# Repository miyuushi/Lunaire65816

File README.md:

# Lunaire65816

My 16-bit retro computer I designed from scratch. It's centered around a 65816 CPU and uses classic components with FPGA-based glue logic, hardware FM sound, and modern display output.

## Features

- 65816 16-bit CPU
- Custom PCB design
- FPGA for glue logic and video generation
- YM3812 FM synthesis sound chip
- Dual VIA chips for I/O
- SNES controller headers
- PS/2 keyboard interface
- VGA output

## Architecture Overview

- CPU: WDC 65816
- Sound: YM3812 (OPL2)
- I/O: Two VIA chips
- Video: VGA generated using FPGA logic
- Input:
  - SNES controller ports
  - PS/2 keyboard
- Address decoding: GAL
- Board: Custom PCB

## Memory Map

Address decoding is handled by a GAL chip.

### 6502 Emulation Mode

- 48K RAM
- 4K I/O
- 12K ROM

This mode is useful for compatibility and early bring-up.

### 65816 Native Mode

- 4MB RAM
- 4K I/O (expandable, may increase later)
- 12K ROM

Native mode enables the full 24-bit address space of the 65816.

## Audio

The system uses a YM3812 (OPL2) FM synthesis chip for hardware-generated sound.

## Input

- SNES controller headers for gamepad input
- PS/2 keyboard support

## Video (unimplemented)

VGA output is generated through FPGA logic. The goal is compatibility with modern monitors. 

## Screenshots

Hardware:

## Hardware Design Notes

- Custom PCB layout
- Discrete retro components
- FPGA used for glue logic and video
- GAL used for address decoding
- VIA chips provide timers and general-purpose I/O

## Status

Work in progress. Basic hardware is assembled and bring-up is ongoing.

## License

This project is licensed under the GNU Lesser General Public License v3.0 or later.

See the LICENSE file for details.

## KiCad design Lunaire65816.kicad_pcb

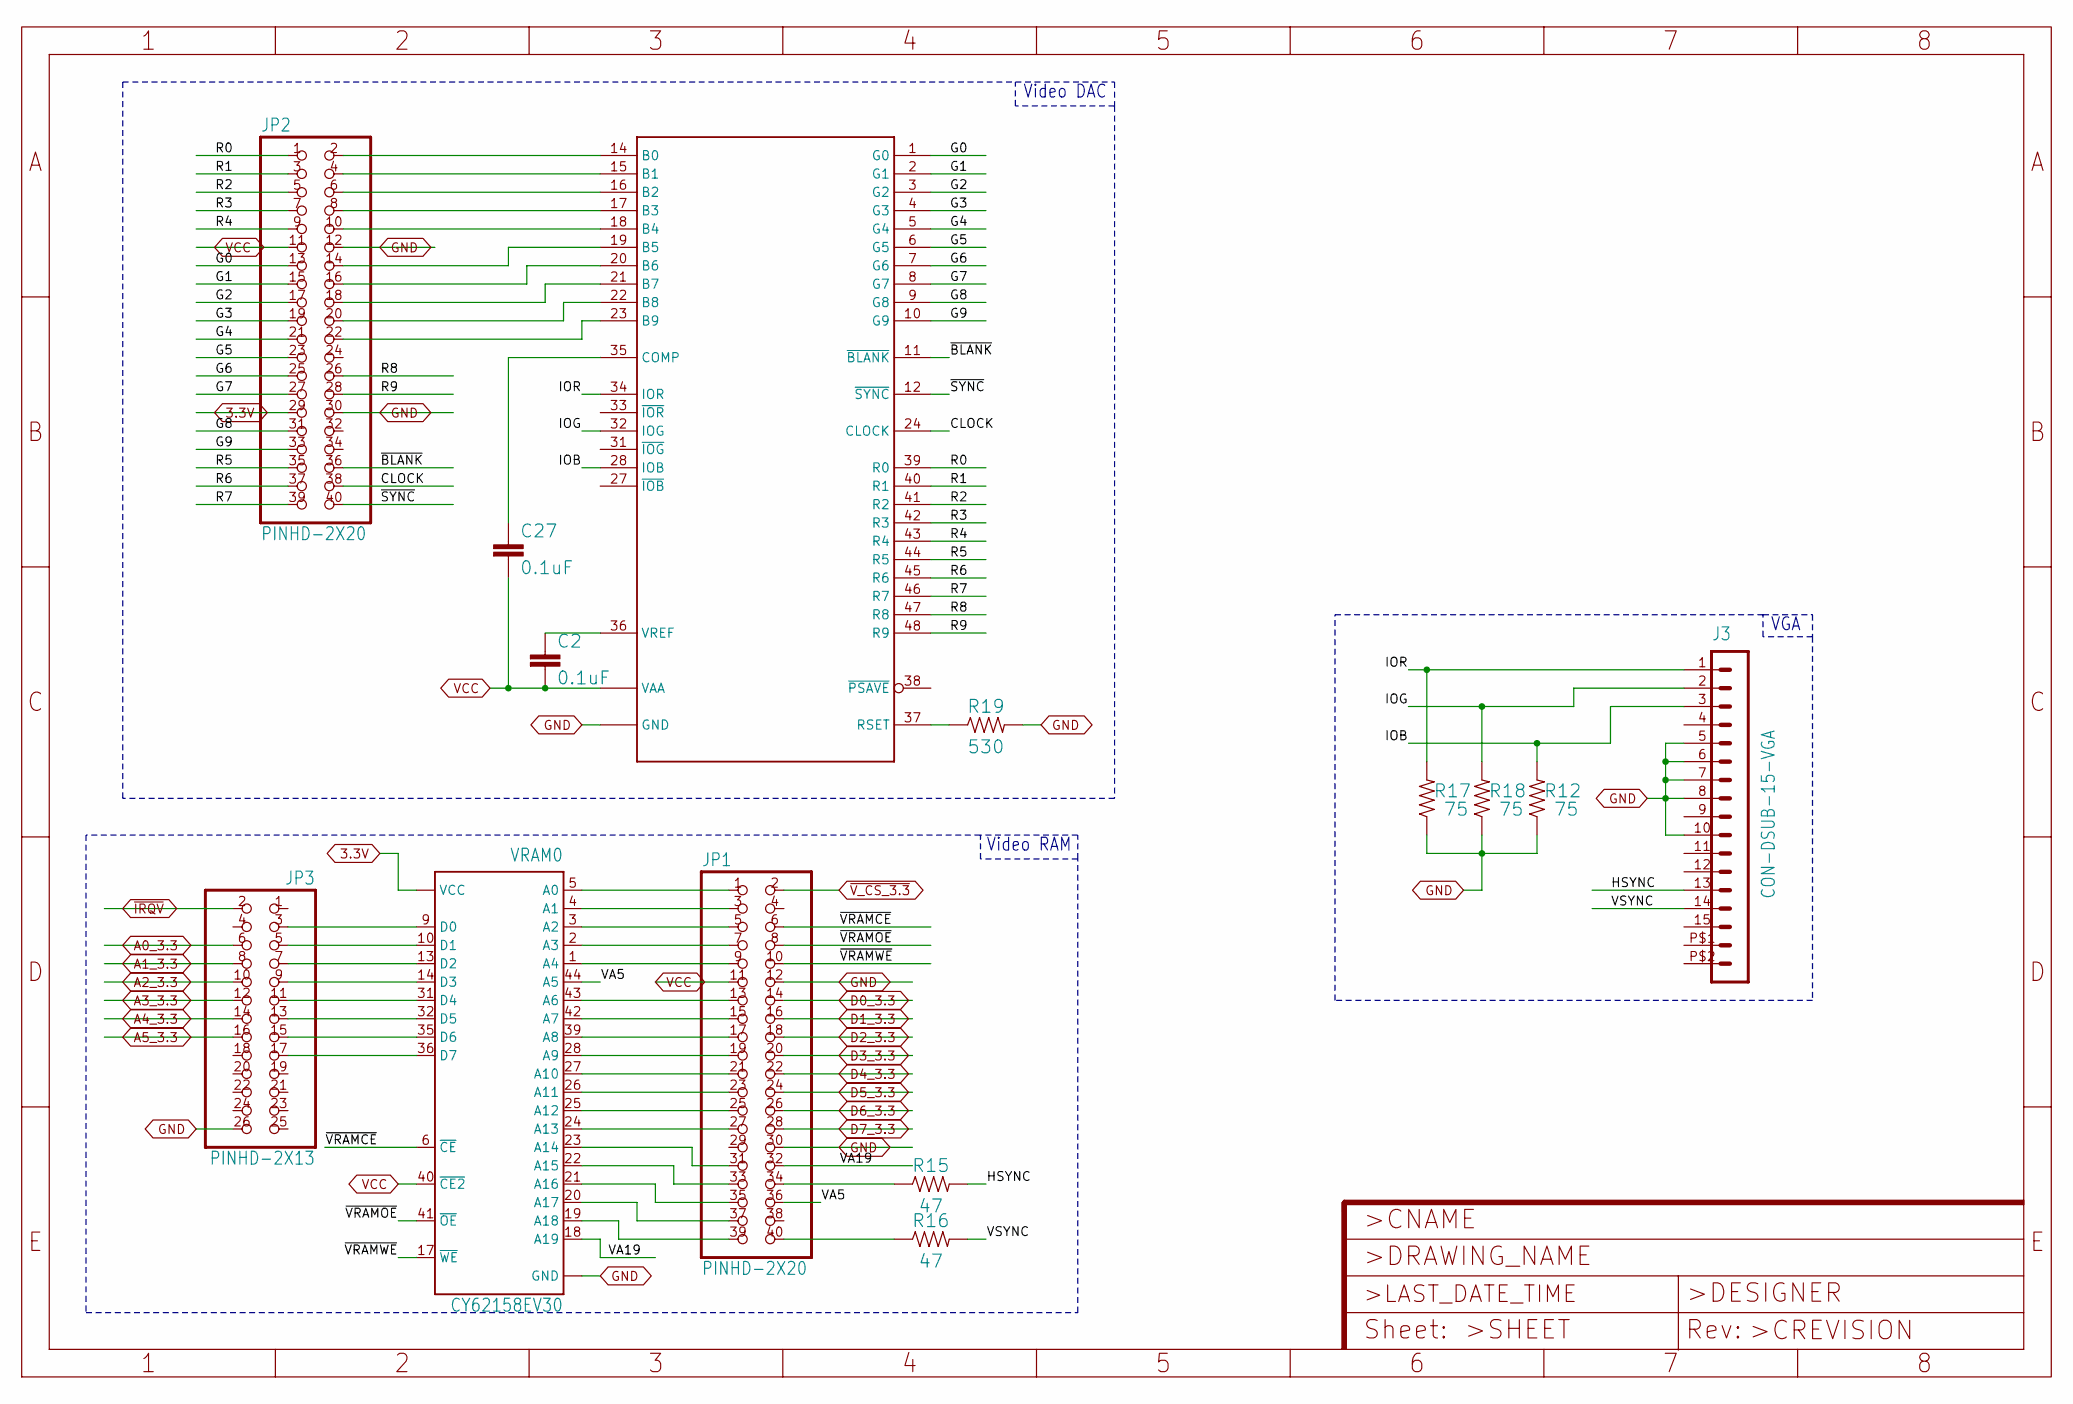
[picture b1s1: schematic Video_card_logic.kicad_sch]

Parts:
C2, C27: 0.1uF; 0603
IC2: ADV7123; LQFP48
J3: CON-DSUB-15-VGA; 181-015-212-171
JP1, JP2: PINHD-2X20; 2X20
JP3: PINHD-2X13; 2X13
R12, R17, R18: 75; 0603
R15, R16: 47; 0603
R19: 530; 0603
VRAM0: CY62158EV30; TSOP-II-44

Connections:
3.3V: JP2.29, VRAM0.11 (VCC), VRAM0.33 (VCC); also elsewhere on the board
A0_3.3: JP3.6; also elsewhere on the board
A1_3.3: JP3.8; also elsewhere on the board
A2_3.3: JP3.10; also elsewhere on the board
A3_3.3: JP3.12; also elsewhere on the board
A4_3.3: JP3.14; also elsewhere on the board
A5_3.3: JP3.16; also elsewhere on the board
CLOCK: IC2.24 (CLOCK), JP2.38
D0_3.3: JP1.14; also elsewhere on the board
D1_3.3: JP1.16; also elsewhere on the board
D2_3.3: JP1.18; also elsewhere on the board
D3_3.3: JP1.20; also elsewhere on the board
D4_3.3: JP1.22; also elsewhere on the board
D5_3.3: JP1.24; also elsewhere on the board
D6_3.3: JP1.26; also elsewhere on the board
D7_3.3: JP1.28; also elsewhere on the board
G0: IC2.1 (G0), JP2.13
G1: IC2.2 (G1), JP2.15
G2: IC2.3 (G2), JP2.17
G3: IC2.4 (G3), JP2.19
G4: IC2.5 (G4), JP2.21
G5: IC2.6 (G5), JP2.23
G6: IC2.7 (G6), JP2.25
G7: IC2.8 (G7), JP2.27
G8: IC2.9 (G8), JP2.31
G9: IC2.10 (G9), JP2.33
GND: IC2.25 (GND), IC2.26 (GND), J3.5, J3.6, J3.7, J3.8, J3.10, JP1.12, JP1.30, JP2.12, JP2.30, JP3.26, R12.1, R17.1, R18.1, R19.2, VRAM0.12 (GND), VRAM0.34 (GND); also elsewhere on the board
HSYNC: J3.13, R15.2
IOB: IC2.28 (IOB), J3.3, R12.2
IOG: IC2.32 (IOG), J3.2, R18.2
IOR: IC2.34 (IOR), J3.1, R17.2
unnamed: JP1.35, VRAM0.21 (A16)
unnamed: JP1.33, VRAM0.22 (A15)
unnamed: JP1.31, VRAM0.23 (A14)
unnamed: JP1.27, VRAM0.24 (A13)
unnamed: IC2.37 (RSET), R19.1
unnamed: C2.1, IC2.36 (VREF)
unnamed: JP1.37, VRAM0.20 (A17)
unnamed: IC2.14 (B0), JP2.2
unnamed: IC2.15 (B1), JP2.4
unnamed: IC2.16 (B2), JP2.6
unnamed: IC2.17 (B3), JP2.8
unnamed: IC2.18 (B4), JP2.10
unnamed: IC2.19 (B5), JP2.14
unnamed: IC2.20 (B6), JP2.16
unnamed: IC2.21 (B7), JP2.18
unnamed: IC2.22 (B8), JP2.20
unnamed: IC2.23 (B9), JP2.22
unnamed: C27.1, IC2.35 (COMP)
unnamed: JP1.40, R16.1
unnamed: JP1.34, R15.1
unnamed: JP1.25, VRAM0.25 (A12)
unnamed: JP1.23, VRAM0.26 (A11)
unnamed: JP1.21, VRAM0.27 (A10)
unnamed: JP1.19, VRAM0.28 (A9)
unnamed: JP1.17, VRAM0.39 (A8)
unnamed: JP1.15, VRAM0.42 (A7)
unnamed: JP1.13, VRAM0.43 (A6)
unnamed: JP1.9, VRAM0.1 (A4)
unnamed: JP1.7, VRAM0.2 (A3)
unnamed: JP1.5, VRAM0.3 (A2)
unnamed: JP3.17, VRAM0.36 (D7)
unnamed: JP3.15, VRAM0.35 (D6)
unnamed: JP3.13, VRAM0.32 (D5)
unnamed: JP3.11, VRAM0.31 (D4)
unnamed: JP3.9, VRAM0.14 (D3)
unnamed: JP3.7, VRAM0.13 (D2)
unnamed: JP3.5, VRAM0.10 (D1)
unnamed: JP3.3, VRAM0.9 (D0)
unnamed: JP1.39, VRAM0.19 (A18)
unnamed: JP1.3, VRAM0.4 (A1)
unnamed: JP1.1, VRAM0.5 (A0)
R0: IC2.39 (R0), JP2.1
R1: IC2.40 (R1), JP2.3
R2: IC2.41 (R2), JP2.5
R3: IC2.42 (R3), JP2.7
R4: IC2.43 (R4), JP2.9
R5: IC2.44 (R5), JP2.35
R6: IC2.45 (R6), JP2.37
R7: IC2.46 (R7), JP2.39
R8: IC2.47 (R8), JP2.26
R9: IC2.48 (R9), JP2.28
VA5: JP1.36, VRAM0.44 (A5)
VA19: JP1.32, VRAM0.18 (A19)
VCC: C2.2, C27.2, IC2.13 (VAA), IC2.29 (VAA), IC2.30 (VAA), JP1.11, JP2.11, VRAM0.40 (~CE2); also elsewhere on the board
VSYNC: J3.14, R16.2
~BLANK: IC2.11 (~BLANK), JP2.36
~IRQV: JP3.2; also elsewhere on the board
~SYNC: IC2.12 (~SYNC), JP2.40
~VRAMCE: JP1.6, VRAM0.6 (~CE)
~VRAMOE: JP1.8, VRAM0.41 (~OE)
~VRAMWE: JP1.10, VRAM0.17 (~WE)
~V_CS_3.3: JP1.2; also elsewhere on the board

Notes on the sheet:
VGA
Video DAC
Video RAM

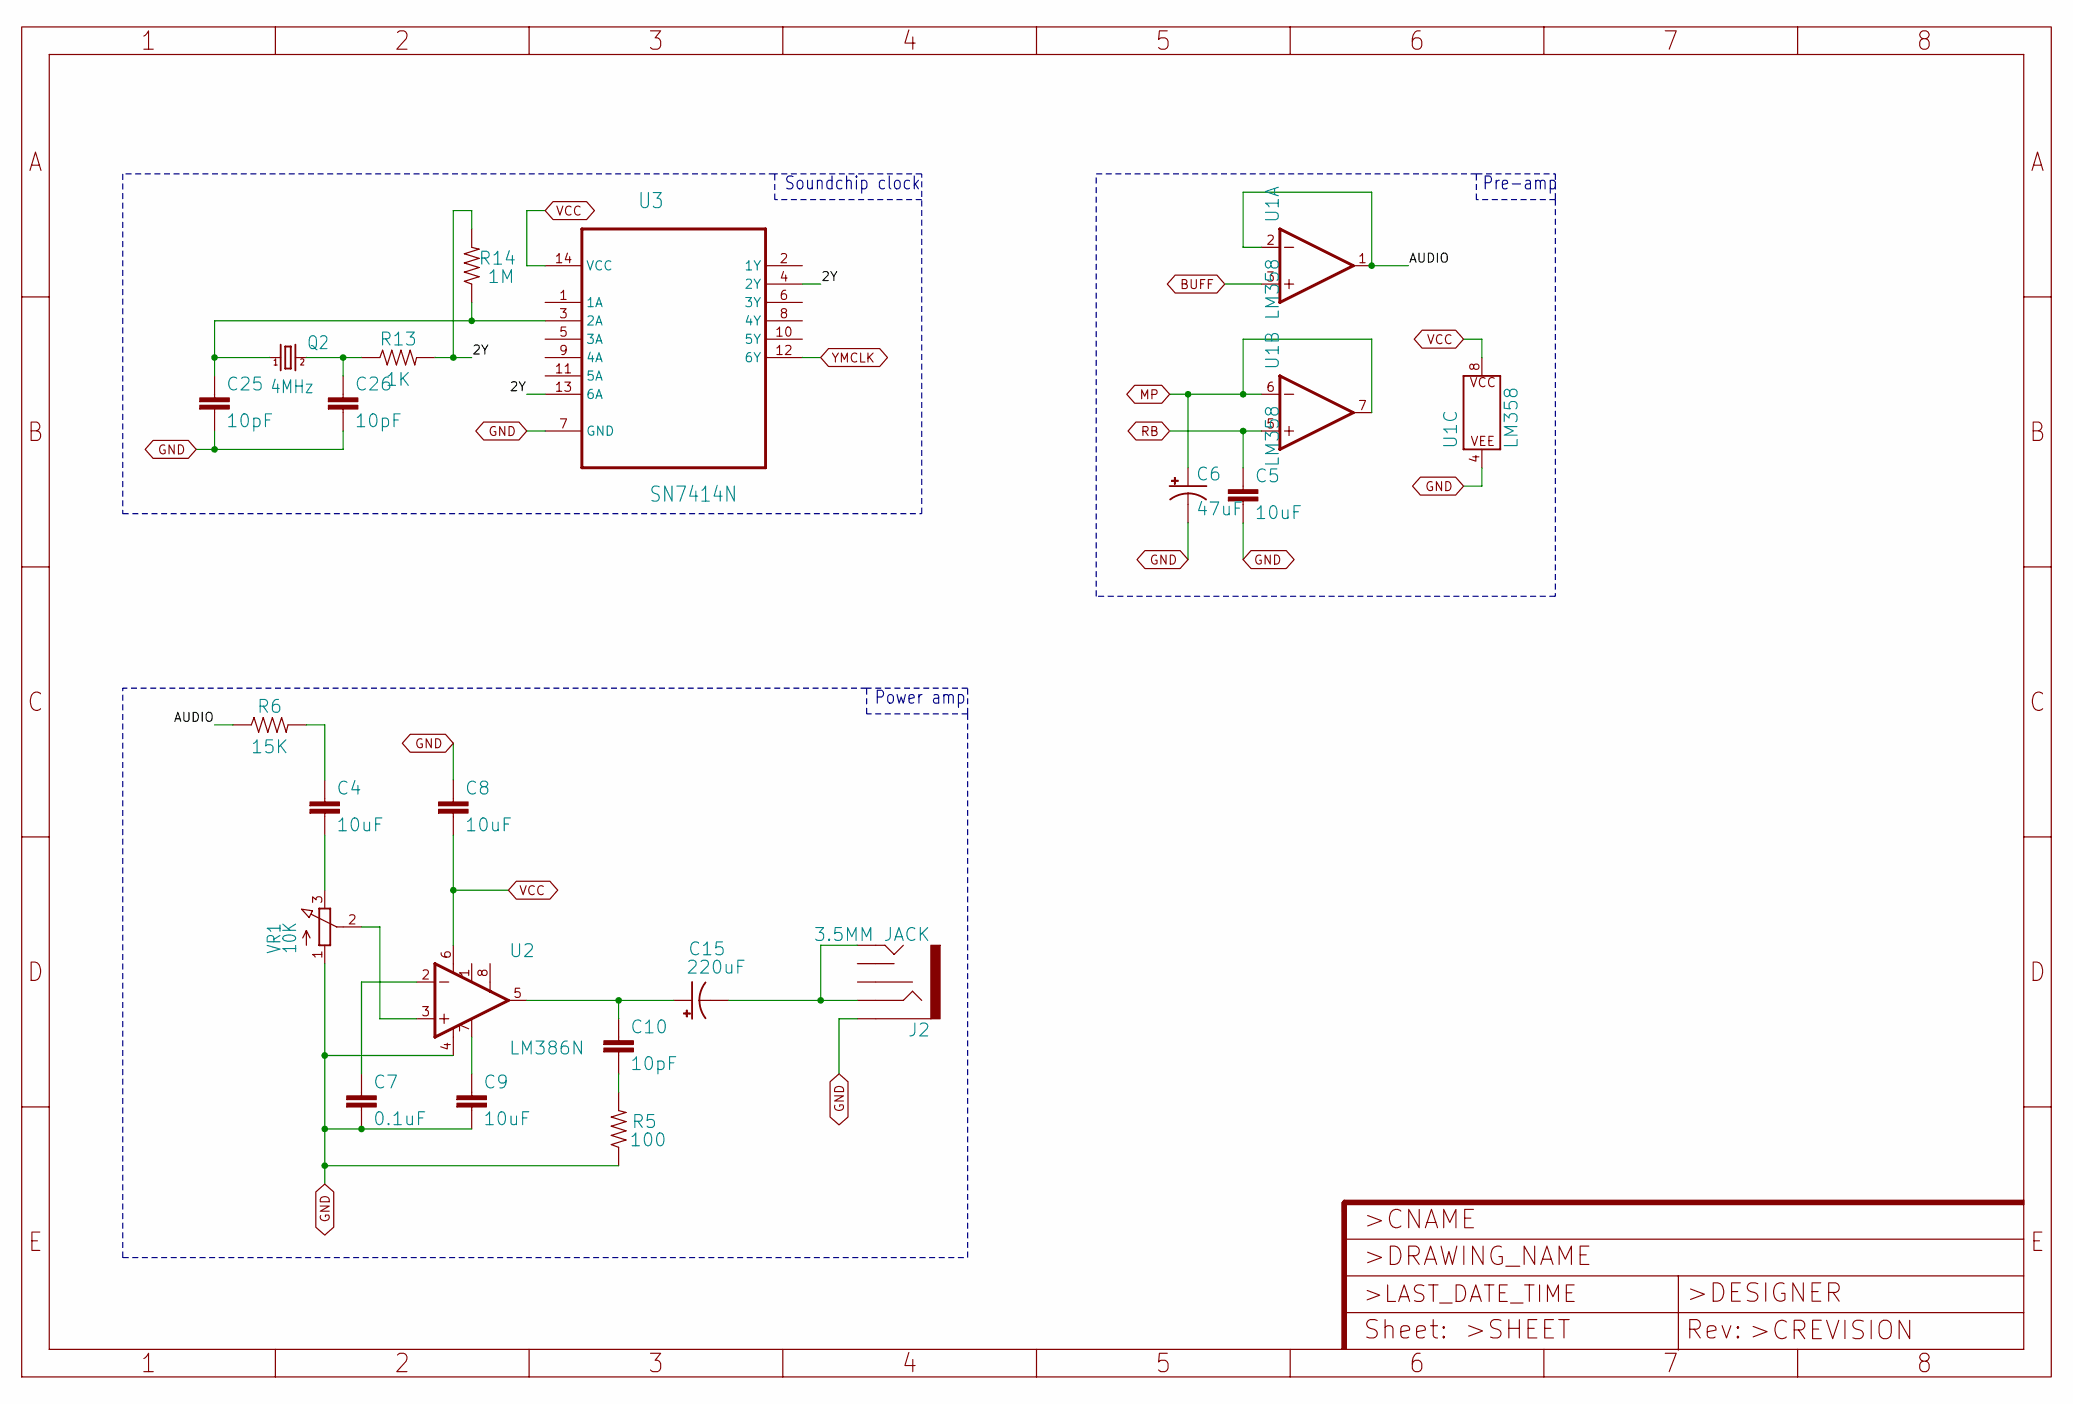
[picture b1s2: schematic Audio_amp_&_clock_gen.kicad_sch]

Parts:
C4, C5, C8, C9: 10uF; 0603
C6: 47uF; EIA3528
C7: 0.1uF; 0603
C10, C25, C26: 10pF; 0603
C15: 220uF; PANASONIC_D
J2: 3.5MM JACK; AUDIO-JACK
Q2: 4MHz; HC49_S
R5: 100; 0603
R6: 15K; 0603
R13: 1K; 0603
R14: 1M; 0603
U1: LM358; DIP08
U2: LM386N; DIP08
U3: SN7414N; DIP254P762X508-14
VR1: 10K; 3RP_1610N

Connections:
2Y: R13.2, R14.2, U3.4 (2Y), U3.13 (6A)
AUDIO: R6.1, U1.1 (OUT), U1.2 (-IN)
BUFF: U1.3 (+IN); also elsewhere on the board
GND: C5.2, C6.C (-), C7.2, C8.1, C9.2, C25.2, C26.2, J2.SLEEVE, R5.1, U1.4 (P$V-), U2.4 (V-), U3.7 (GND), VR1.1 (A); also elsewhere on the board
MP: C6.A (+), U1.6 (-IN), U1.7 (OUT); also elsewhere on the board
unnamed: C7.1, U2.2 (-IN)
unnamed: C4.1, R6.2
unnamed: C4.2, VR1.3 (E)
unnamed: U2.3 (+IN), VR1.2 (S)
unnamed: C9.1, U2.7 (BP)
unnamed: C10.1, C15.+, U2.5 (OUT)
unnamed: C10.2, R5.2
unnamed: C15.-, J2.RING, J2.TIP
unnamed: C25.1, Q2.1, R14.1, U3.3 (2A)
unnamed: C26.1, Q2.2, R13.1
RB: C5.1, U1.5 (+IN); also elsewhere on the board
VCC: C8.2, U1.8 (P$V+), U2.6 (V+), U3.14 (VCC); also elsewhere on the board
YMCLK: U3.12 (6Y); also elsewhere on the board

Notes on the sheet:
Power amp
Soundchip clock
Pre-amp

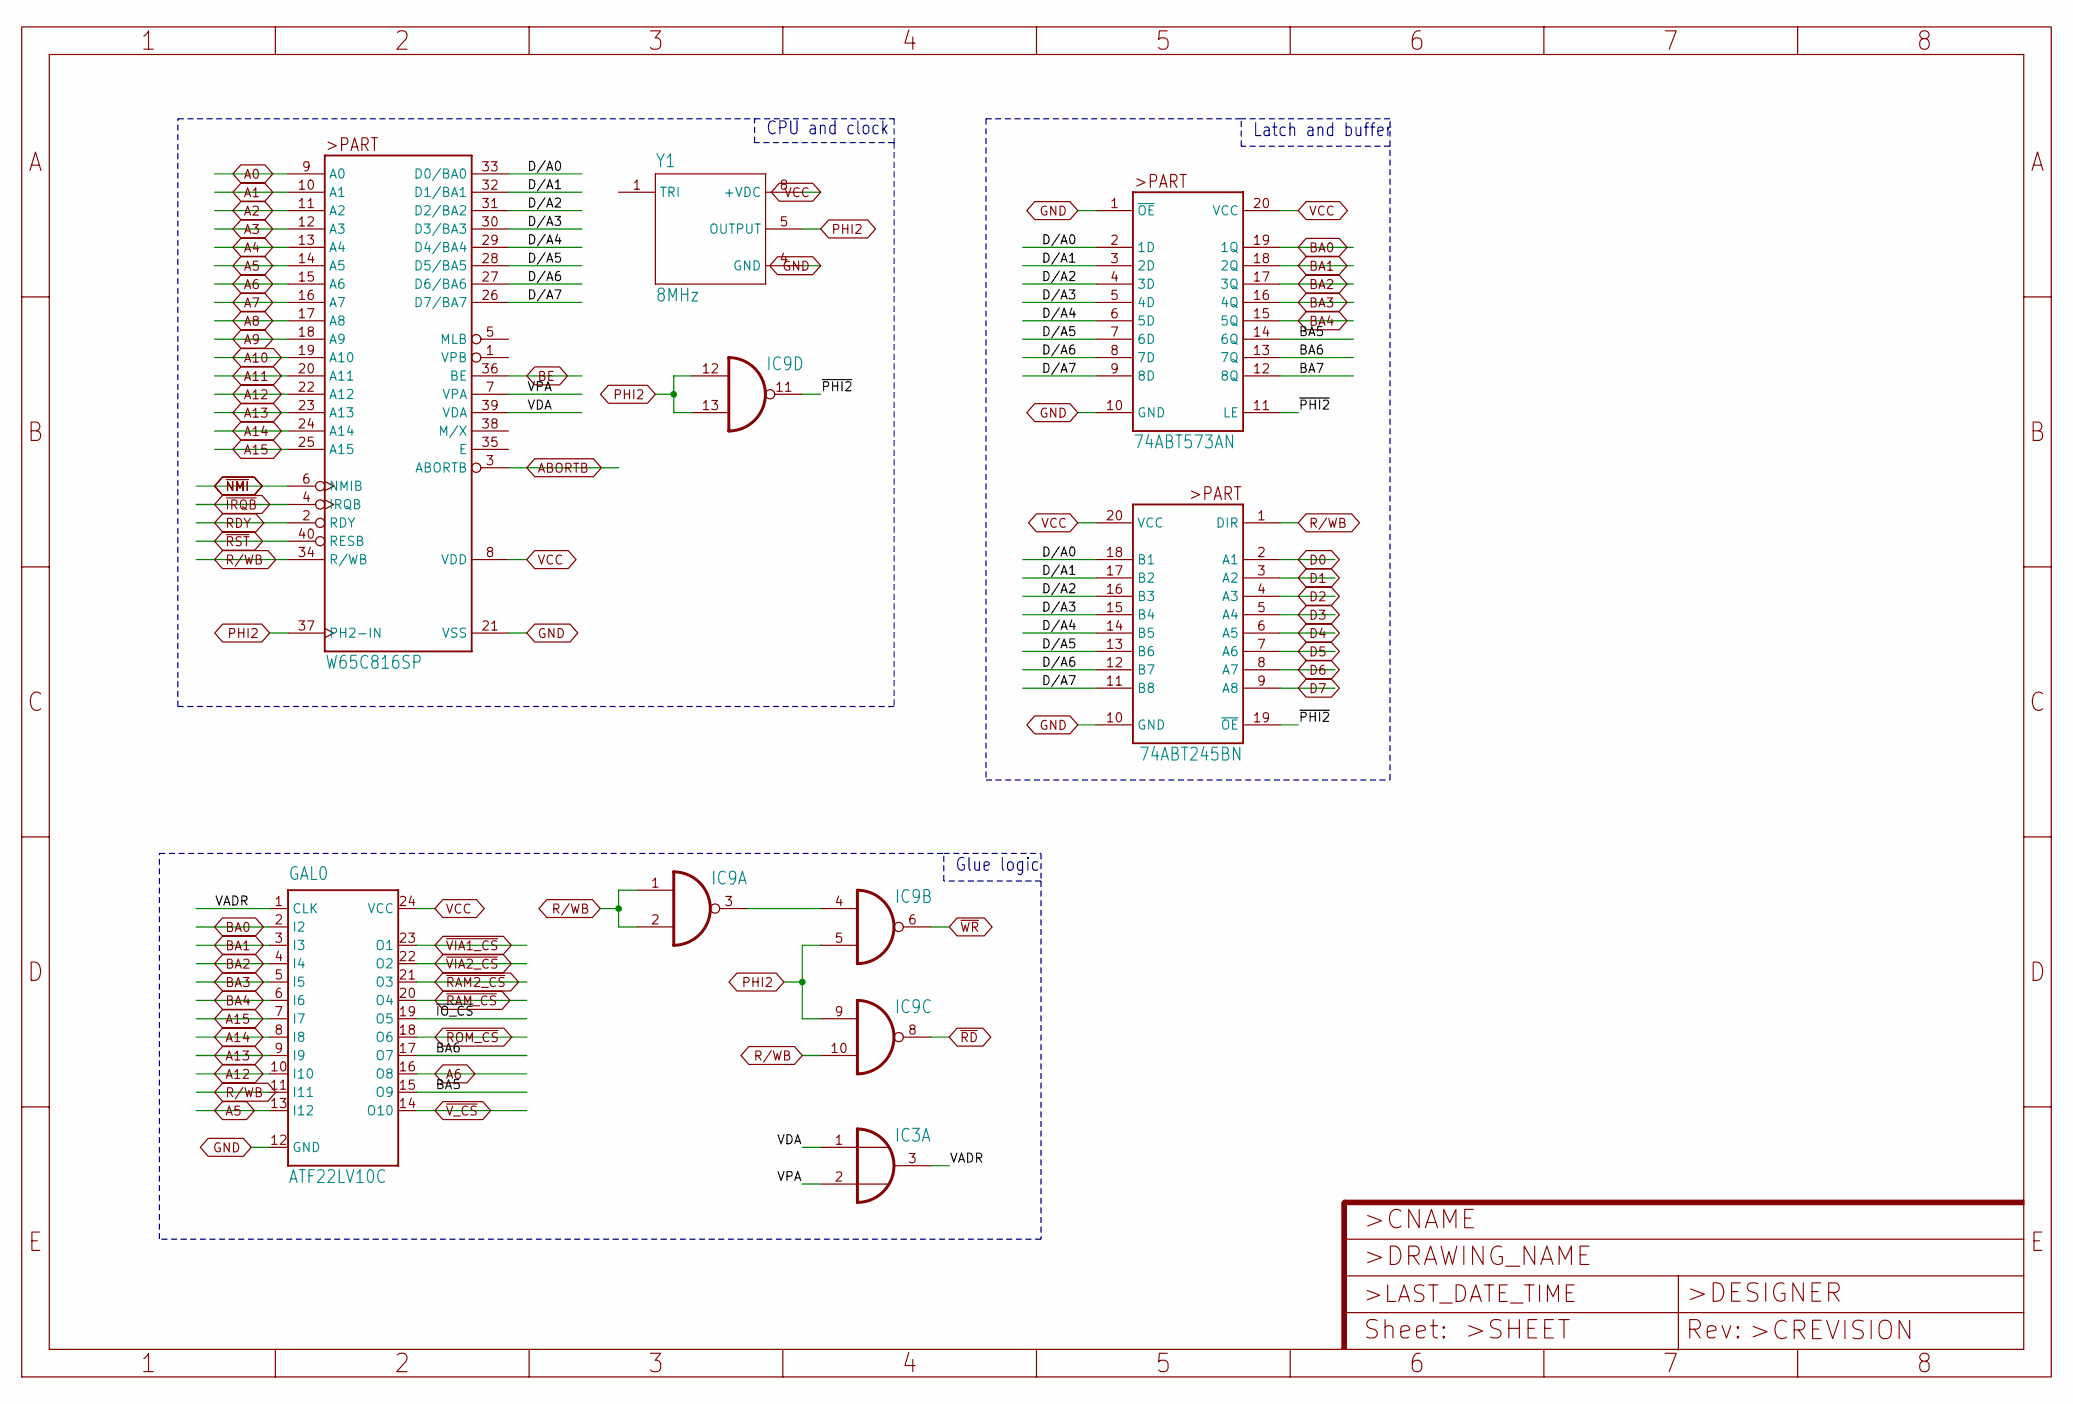
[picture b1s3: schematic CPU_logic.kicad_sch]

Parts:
BUFF_DAT0: 74ABT245BN; PDIP20
CPU0: W65C816SP; DIP-40
GAL0: ATF22LV10C; DIL24-3
IC3: 7432N; DIL14
IC9: 7400N; DIL14
LATCH_ADDR0: 74ABT573AN; PDIP20
Y1: 8MHz; OSC_ECS-2200B-110.5

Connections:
A0: CPU0.9 (A0); also elsewhere on the board
A1: CPU0.10 (A1); also elsewhere on the board
A2: CPU0.11 (A2); also elsewhere on the board
A3: CPU0.12 (A3); also elsewhere on the board
A4: CPU0.13 (A4); also elsewhere on the board
A5: CPU0.14 (A5), GAL0.13 (I12); also elsewhere on the board
A6: CPU0.15 (A6), GAL0.16 (O8); also elsewhere on the board
A7: CPU0.16 (A7); also elsewhere on the board
A8: CPU0.17 (A8); also elsewhere on the board
A9: CPU0.18 (A9); also elsewhere on the board
A10: CPU0.19 (A10); also elsewhere on the board
A11: CPU0.20 (A11); also elsewhere on the board
A12: CPU0.22 (A12), GAL0.10 (I10); also elsewhere on the board
A13: CPU0.23 (A13), GAL0.9 (I9); also elsewhere on the board
A14: CPU0.24 (A14), GAL0.8 (I8); also elsewhere on the board
A15: CPU0.25 (A15), GAL0.7 (I7); also elsewhere on the board
ABORTB: CPU0.3 (ABORTB); also elsewhere on the board
BA0: GAL0.2 (I2), LATCH_ADDR0.19 (1Q); also elsewhere on the board
BA1: GAL0.3 (I3), LATCH_ADDR0.18 (2Q); also elsewhere on the board
BA2: GAL0.4 (I4), LATCH_ADDR0.17 (3Q); also elsewhere on the board
BA3: GAL0.5 (I5), LATCH_ADDR0.16 (4Q); also elsewhere on the board
BA4: GAL0.6 (I6), LATCH_ADDR0.15 (5Q); also elsewhere on the board
BA5: GAL0.15 (O9), LATCH_ADDR0.14 (6Q)
BA6: GAL0.17 (O7), LATCH_ADDR0.13 (7Q)
BA7: LATCH_ADDR0.12 (8Q)
BE: CPU0.36 (BE); also elsewhere on the board
D0: BUFF_DAT0.2 (A1); also elsewhere on the board
D1: BUFF_DAT0.3 (A2); also elsewhere on the board
D2: BUFF_DAT0.4 (A3); also elsewhere on the board
D3: BUFF_DAT0.5 (A4); also elsewhere on the board
D4: BUFF_DAT0.6 (A5); also elsewhere on the board
D5: BUFF_DAT0.7 (A6); also elsewhere on the board
D6: BUFF_DAT0.8 (A7); also elsewhere on the board
D7: BUFF_DAT0.9 (A8); also elsewhere on the board
D/A0: BUFF_DAT0.18 (B1), CPU0.33 (D0/BA0), LATCH_ADDR0.2 (1D)
D/A1: BUFF_DAT0.17 (B2), CPU0.32 (D1/BA1), LATCH_ADDR0.3 (2D)
D/A2: BUFF_DAT0.16 (B3), CPU0.31 (D2/BA2), LATCH_ADDR0.4 (3D)
D/A3: BUFF_DAT0.15 (B4), CPU0.30 (D3/BA3), LATCH_ADDR0.5 (4D)
D/A4: BUFF_DAT0.14 (B5), CPU0.29 (D4/BA4), LATCH_ADDR0.6 (5D)
D/A5: BUFF_DAT0.13 (B6), CPU0.28 (D5/BA5), LATCH_ADDR0.7 (6D)
D/A6: BUFF_DAT0.12 (B7), CPU0.27 (D6/BA6), LATCH_ADDR0.8 (7D)
D/A7: BUFF_DAT0.11 (B8), CPU0.26 (D7/BA7), LATCH_ADDR0.9 (8D)
GND: BUFF_DAT0.10 (GND), CPU0.21 (VSS), GAL0.12 (GND), IC3.7 (GND), IC9.7 (GND), LATCH_ADDR0.1 (~OE), LATCH_ADDR0.10 (GND), Y1.4 (GND); also elsewhere on the board
unnamed: IC9.3 (O), IC9.4 (I0)
PHI2: CPU0.37 (PH2-IN), IC9.5 (I1), IC9.9 (I0), IC9.12 (I0), IC9.13 (I1), Y1.5 (OUTPUT); also elsewhere on the board
R/WB: BUFF_DAT0.1 (DIR), CPU0.34 (R/WB), GAL0.11 (I11), IC9.1 (I0), IC9.2 (I1), IC9.10 (I1); also elsewhere on the board
RDY: CPU0.2 (RDY); also elsewhere on the board
VADR: GAL0.1 (CLK), IC3.3 (O)
VCC: BUFF_DAT0.20 (VCC), CPU0.8 (VDD), GAL0.24 (VCC), IC3.14 (VCC), IC9.14 (VCC), LATCH_ADDR0.20 (VCC), Y1.8 (+VDC); also elsewhere on the board
VDA: CPU0.39 (VDA), IC3.1 (I0)
VPA: CPU0.7 (VPA), IC3.2 (I1)
~IO_CS: GAL0.19 (O5)
~IRQB: CPU0.4 (IRQB); also elsewhere on the board
~NMI: CPU0.6 (NMIB); also elsewhere on the board
~PHI2: BUFF_DAT0.19 (~OE), IC9.11 (O), LATCH_ADDR0.11 (LE)
~RAM2_CS: GAL0.21 (O3); also elsewhere on the board
~RAM_CS: GAL0.20 (O4); also elsewhere on the board
~RD: IC9.8 (O); also elsewhere on the board
~ROM_CS: GAL0.18 (O6); also elsewhere on the board
~RST: CPU0.40 (RESB); also elsewhere on the board
~VIA1_CS: GAL0.23 (O1); also elsewhere on the board
~VIA2_CS: GAL0.22 (O2); also elsewhere on the board
~V_CS: GAL0.14 (O10); also elsewhere on the board
~WR: IC9.6 (O); also elsewhere on the board

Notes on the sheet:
CPU and clock
Latch and buffer
Glue logic

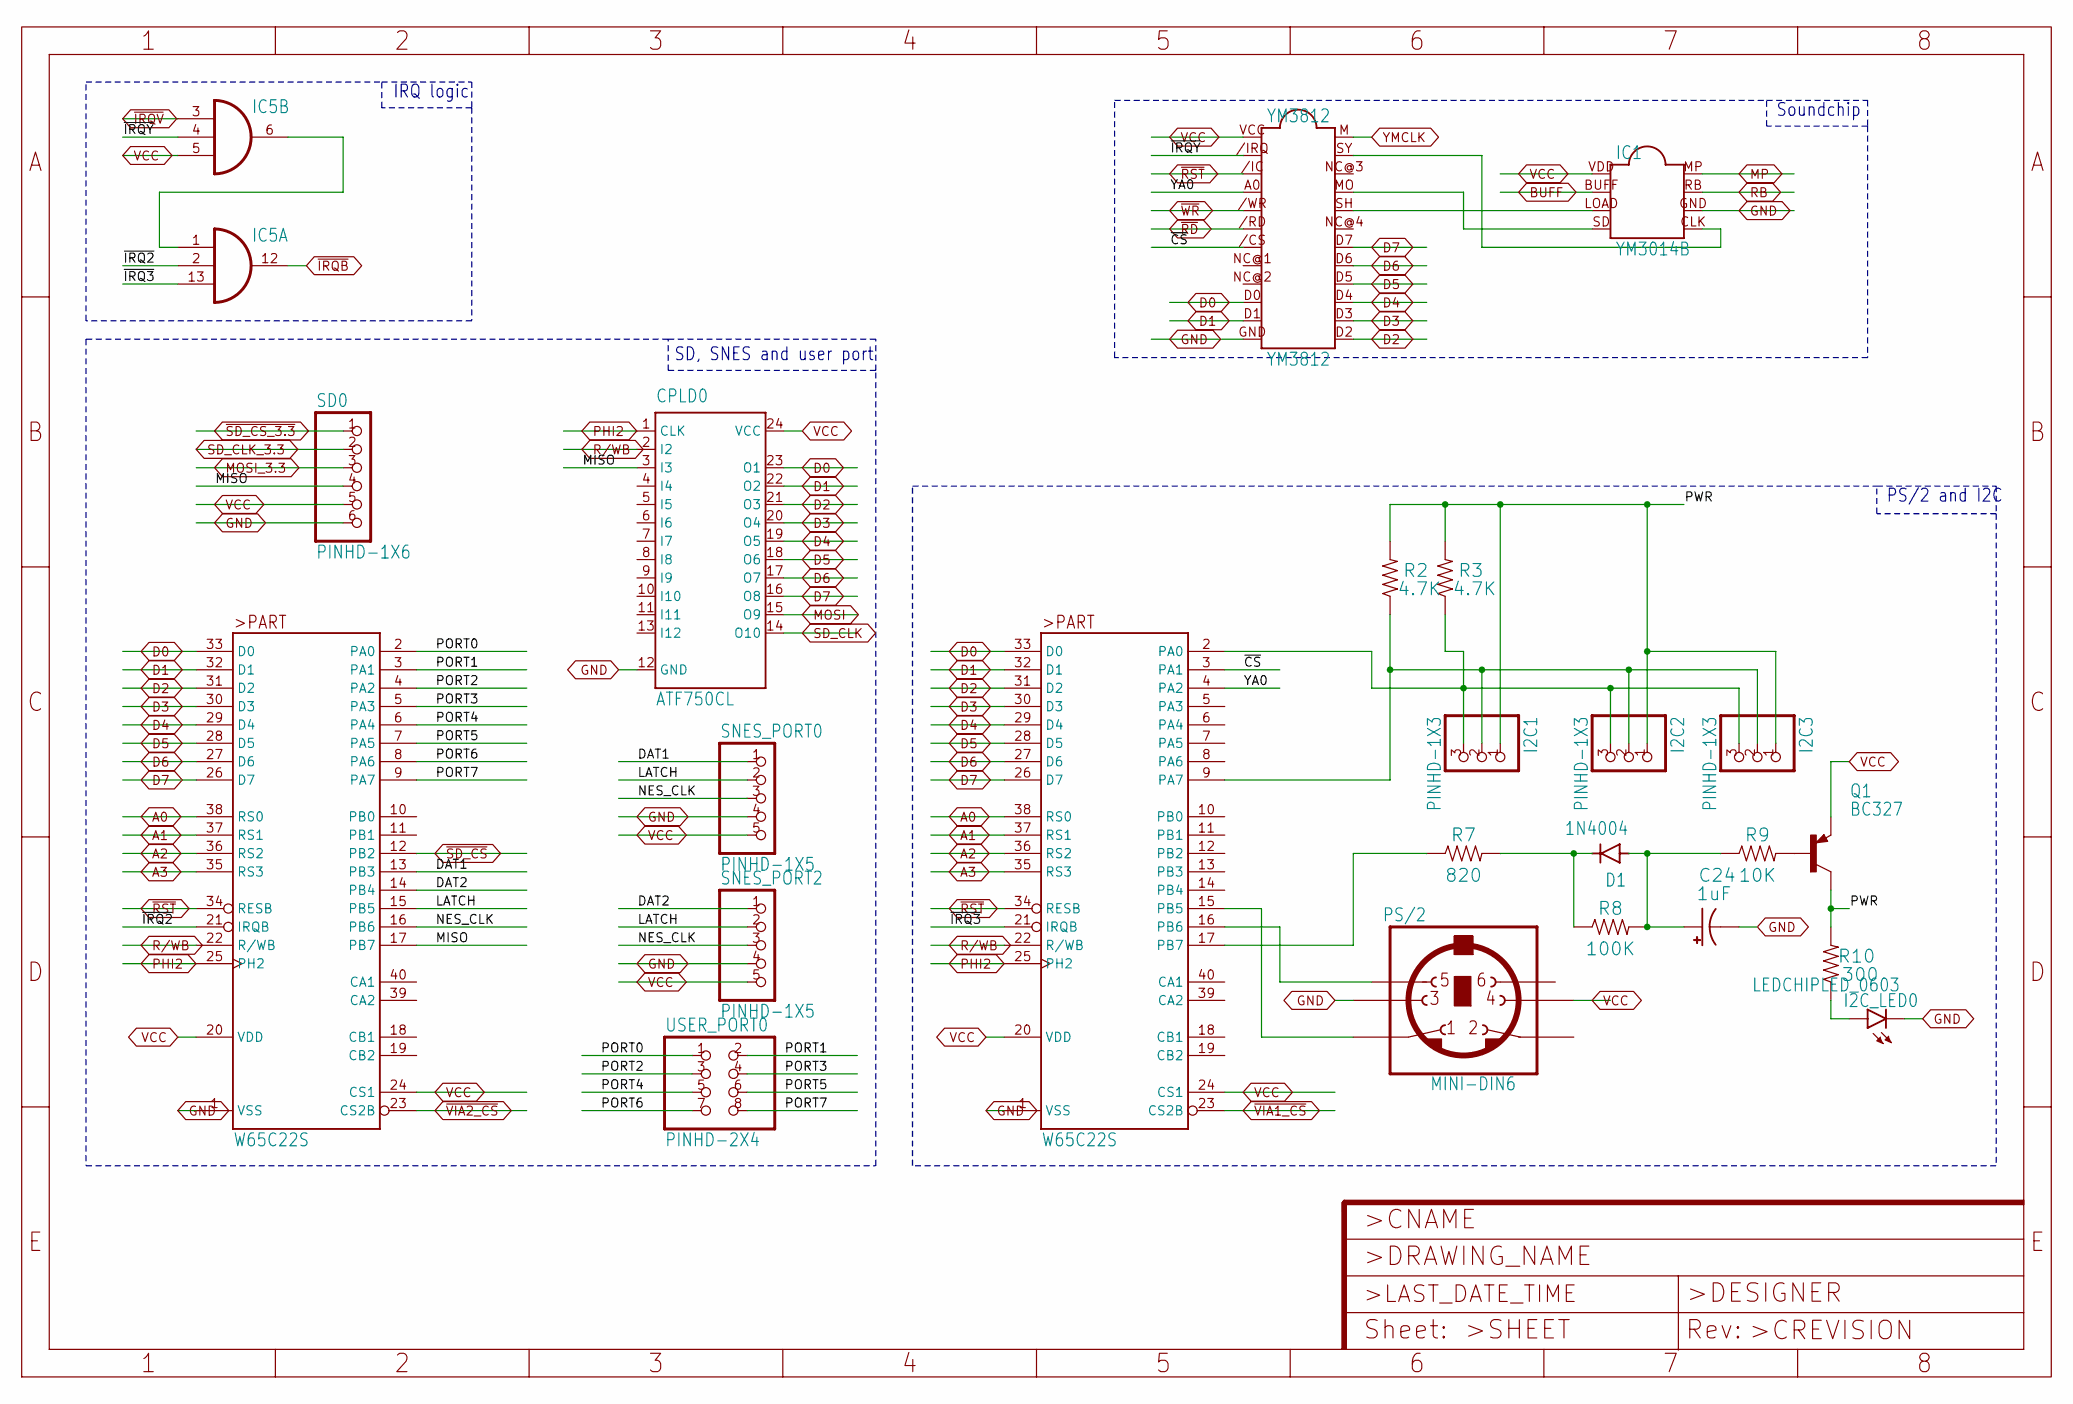
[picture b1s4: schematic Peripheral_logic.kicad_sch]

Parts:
C24: 1uF; EIA3528
CPLD0: ATF750CL; DIL24-3
D1: 1N4004; DO-41
I2C1, I2C2, I2C3: PINHD-1X3; 1X03
I2C_LED0: LEDCHIPLED_0603; CHIPLED_0603
IC1: YM3014B
IC5: 7411N; DIL14
PS/2: MINI-DIN6
Q1: BC327; TO92-EBC
R2, R3: 4.7K; 0603
R7: 820; 0603
R8: 100K; 0603
R9: 10K; 0603
R10: 300; 0603
SD0: PINHD-1X6; 1X06
SNES_PORT0, SNES_PORT2: PINHD-1X5; 1X05
USER_PORT0: PINHD-2X4; 2X04
VIA1, VIA2: W65C22S; DIP-40
YM3812: YM3812

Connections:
A0: VIA1.38 (RS0), VIA2.38 (RS0); also elsewhere on the board
A1: VIA1.37 (RS1), VIA2.37 (RS1); also elsewhere on the board
A2: VIA1.36 (RS2), VIA2.36 (RS2); also elsewhere on the board
A3: VIA1.35 (RS3), VIA2.35 (RS3); also elsewhere on the board
BUFF: IC1.BUFF; also elsewhere on the board
CLK: I2C1.3, I2C2.3, I2C3.3, R3.1, VIA1.2 (PA0)
D0: CPLD0.23 (O1), VIA1.33 (D0), VIA2.33 (D0), YM3812.D0; also elsewhere on the board
D1: CPLD0.22 (O2), VIA1.32 (D1), VIA2.32 (D1), YM3812.D1; also elsewhere on the board
D2: CPLD0.21 (O3), VIA1.31 (D2), VIA2.31 (D2), YM3812.D2; also elsewhere on the board
D3: CPLD0.20 (O4), VIA1.30 (D3), VIA2.30 (D3), YM3812.D3; also elsewhere on the board
D4: CPLD0.19 (O5), VIA1.29 (D4), VIA2.29 (D4), YM3812.D4; also elsewhere on the board
D5: CPLD0.18 (O6), VIA1.28 (D5), VIA2.28 (D5), YM3812.D5; also elsewhere on the board
D6: CPLD0.17 (O7), VIA1.27 (D6), VIA2.27 (D6), YM3812.D6; also elsewhere on the board
D7: CPLD0.16 (O8), VIA1.26 (D7), VIA2.26 (D7), YM3812.D7; also elsewhere on the board
DAT1: SNES_PORT0.1, VIA2.13 (PB3)
DAT2: SNES_PORT2.1, VIA2.14 (PB4)
DATA: I2C1.2, I2C2.2, I2C3.2, R2.1, VIA1.9 (PA7)
GND: C24.C (-), CPLD0.12 (GND), I2C_LED0.C, IC1.GND, IC5.7 (GND), PS/2.3, SD0.6, SNES_PORT0.4, SNES_PORT2.4, VIA1.1 (VSS), VIA2.1 (VSS), YM3812.GND; also elsewhere on the board
LATCH: SNES_PORT0.2, SNES_PORT2.2, VIA2.15 (PB5)
MISO: CPLD0.3 (I3), SD0.4, VIA2.17 (PB7)
MOSI: CPLD0.15 (O9); also elsewhere on the board
MOSI_3.3: SD0.3; also elsewhere on the board
MP: IC1.MP; also elsewhere on the board
unnamed: IC1.LOAD, YM3812.SH
unnamed: IC1.SD, YM3812.MO
unnamed: PS/2.1, VIA1.15 (PB5)
unnamed: PS/2.5, VIA1.16 (PB6)
unnamed: R7.1, VIA1.17 (PB7)
unnamed: D1.C, R7.2, R8.1
unnamed: C24.A (+), D1.A, R8.2, R9.1
unnamed: Q1.B, R9.2
unnamed: I2C_LED0.A, R10.1
unnamed: IC1.CLK, YM3812.SY
unnamed: IC5.1 (I0), IC5.6 (O)
NES_CLK: SNES_PORT0.3, SNES_PORT2.3, VIA2.16 (PB6)
PHI2: CPLD0.1 (CLK), VIA1.25 (PH2), VIA2.25 (PH2); also elsewhere on the board
PORT0: USER_PORT0.1, VIA2.2 (PA0)
PORT1: USER_PORT0.2, VIA2.3 (PA1)
PORT2: USER_PORT0.3, VIA2.4 (PA2)
PORT3: USER_PORT0.4, VIA2.5 (PA3)
PORT4: USER_PORT0.5, VIA2.6 (PA4)
PORT5: USER_PORT0.6, VIA2.7 (PA5)
PORT6: USER_PORT0.7, VIA2.8 (PA6)
PORT7: USER_PORT0.8, VIA2.9 (PA7)
PWR: I2C1.1, I2C2.1, I2C3.1, Q1.C, R2.2, R3.2, R10.2
R/WB: CPLD0.2 (I2), VIA1.22 (R/WB), VIA2.22 (R/WB); also elsewhere on the board
RB: IC1.RB; also elsewhere on the board
SD_CLK: CPLD0.14 (O10); also elsewhere on the board
SD_CLK_3.3: SD0.2; also elsewhere on the board
VCC: CPLD0.24 (VCC), IC1.VDD, IC5.5 (I2), IC5.14 (VCC), PS/2.4, Q1.E, SD0.5, SNES_PORT0.5, SNES_PORT2.5, VIA1.20 (VDD), VIA1.24 (CS1), VIA2.20 (VDD), VIA2.24 (CS1), YM3812.VCC; also elsewhere on the board
YA0: VIA1.4 (PA2), YM3812.A0
YMCLK: YM3812.M; also elsewhere on the board
~CS: VIA1.3 (PA1), YM3812./CS
~IRQ2: IC5.2 (I1), VIA2.21 (IRQB)
~IRQ3: IC5.13 (I2), VIA1.21 (IRQB)
~IRQB: IC5.12 (O); also elsewhere on the board
~IRQV: IC5.3 (I0); also elsewhere on the board
~IRQY: IC5.4 (I1), YM3812./IRQ
~RD: YM3812./RD; also elsewhere on the board
~RST: VIA1.34 (RESB), VIA2.34 (RESB), YM3812./IC; also elsewhere on the board
~SD_CS_3.3: SD0.1; also elsewhere on the board
~SD_CS: VIA2.12 (PB2); also elsewhere on the board
~VIA1_CS: VIA1.23 (CS2B); also elsewhere on the board
~VIA2_CS: VIA2.23 (CS2B); also elsewhere on the board
~WR: YM3812./WR; also elsewhere on the board

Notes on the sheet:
Soundchip
SD, SNES and user port
PS/2 and I2C
IRQ logic
